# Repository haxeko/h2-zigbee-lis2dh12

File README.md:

# Activity Badge — ESP32-H2 + LIS2DH12 + Zigbee

Thẻ đeo (wearable badge) giám sát mức độ hoạt động của công nhân trên công trình.
LIS2DH12 lấy mẫu gia tốc liên tục ở 1 Hz, ESP32-H2 tính `activity_score` mỗi phút và gửi về
Zigbee2MQTT với vai trò Zigbee Sleepy End Device, chạy bằng pin LiPo.

```
        USB-C 5 V                       3V3
   ┌──────────────┐   VBAT   ┌─────────┐      ┌──────────────────────┐   802.15.4
   │ MCP73831     ├────┬─────┤ RT9080  ├──┬───┤ ESP32-H2-WROOM-02C   │ ))) Zigbee ──► router ──► Zigbee2MQTT ──► MQTT
   │ sạc LiPo     │    │     │ LDO 3V3 │  │   │  GPIO4/5   I2C       │
   └──────────────┘  LiPo    └─────────┘  │   │  GPIO10    INT1 (đánh thức)
                    500 mAh               │   │  GPIO1/0   đo pin    │
                                          │   └──────────┬───────────┘
                                          │              │ I2C + INT1
                                          │   ┌──────────┴───────────┐
                                          └───┤ LIS2DH12             │  1 Hz, low-power, FIFO 32 mẫu
                                              └──────────────────────┘
```

## Thuật toán

```
a_mag = sqrt(ax² + ay² + az²)
a_dyn = |a_mag − 1 g|
sum_dyn += a_dyn ; sample_count += 1        (60 mẫu, lưu trong RTC memory)
activity_score = sum_dyn / sample_count     → gửi Zigbee → reset
```

## Nội dung repo

| Thư mục | Nội dung | Tài liệu |
|---|---|---|
| [`hardware/`](hardware/) | Project KiCad: schematic + **PCB 20 × 36 mm, 4 lớp, đã đi dây**, Gerber, BOM, toạ độ linh kiện | [hardware/README.md](hardware/README.md) |
| [`firmware/`](firmware/) | Project ESP-IDF cho ESP32-H2 (esp-zigbee-sdk 2.x) | [firmware/README.md](firmware/README.md) |
| [`zigbee2mqtt/`](zigbee2mqtt/) | External converter cho Zigbee2MQTT + test | [docs/zigbee2mqtt.md](docs/zigbee2mqtt.md) |
| [`docs/`](docs/) | Ước tính dòng tiêu thụ/pin, hướng dẫn join và kiểm thử | [docs/power.md](docs/power.md) |

## Bắt đầu nhanh

1. **Phần cứng**: mở `hardware/kicad/activity-badge.kicad_pro` bằng KiCad 7 trở lên (schematic và
   PCB). File sản xuất nằm ở `hardware/out/fab/`; đọc mục 9 của `hardware/README.md` trước khi đặt hàng.
2. **Firmware** (ESP-IDF v5.5 trở lên):

   ```bash
   cd firmware && idf.py set-target esp32h2 && idf.py build
   ```
   Nạp: giữ BOOT, nhấn RESET, thả BOOT, rồi `idf.py -p /dev/ttyACM0 flash`.
3. **Zigbee2MQTT**: chép `zigbee2mqtt/activity_badge.mjs` vào `external_converters/`, bật
   `advanced.enable_external_js`, bật Permit join, cấp nguồn cho badge.
4. Dữ liệu xuất hiện mỗi phút trên `zigbee2mqtt/<tên badge>`:

   ```json
   {"activity_score": 0.127, "battery": 86, "voltage": 4000, "linkquality": 120}
   ```

## Các quyết định thiết kế chính

| Quyết định | Lý do |
|---|---|
| Cảm biến lấy mẫu vào FIFO, MCU chỉ dậy 2 lần/phút theo ngắt watermark INT1 | MCU không phải dậy 60 lần/phút; LIS2DH12 chỉ tốn ~2 µA |
| INT1 nối vào GPIO10 | Chỉ GPIO7–14 (LP GPIO) đánh thức được ESP32-H2 khỏi deep sleep |
| `activity_score` gửi qua Analog Input (0x000C) PresentValue, pin qua Power Configuration (0x0001) | Cluster chuẩn, converter Z2M chỉ vài dòng |
| Firmware tự gửi Report Attributes tới coordinator | Không phụ thuộc binding/configure reporting, vốn dễ lỡ với thiết bị ngủ |
| Hai chế độ ngủ chọn bằng Kconfig: deep sleep (mặc định, theo đề bài) và light sleep | Ước tính light sleep cho thời lượng pin dài hơn ~4–5 lần ở chu kỳ 1 phút; xem [docs/power.md](docs/power.md) |
| LDO Iq 2 µA, mạch đo pin có công tắc, không thạch anh 32 kHz | Giảm dòng nền và BOM |
| PCB 20 × 36 mm, linh kiện một mặt, pin hàn dây ở mặt dưới, anten nhô khỏi mép board | Gọn (nằm trong diện tích cell 500 mAh), lắp ráp rẻ, anten không bị đồng và FR-4 che |

## Trạng thái kiểm chứng

| Hạng mục | Trạng thái |
|---|---|
| Firmware build (ESP-IDF v5.5.4, esp-zigbee-lib 2.1.0), cả deep sleep, light sleep và bản release | Đã build, không warning trong mã project |
| Thuật toán activity | Unit test trên PC (so với công thức số thực trên 200 000 mẫu ngẫu nhiên) |
| Converter Zigbee2MQTT | Chạy thử với zigbee-herdsman-converters 26.129.0 bằng báo cáo giả lập |
| Schematic KiCad | Netlist xuất từ KiCad được so khớp tự động với netlist thiết kế; ERC chưa chạy |
| PCB KiCad | DRC của KiCad: 0 lỗi, 0 net chưa nối; net của 155 pad khớp với schematic. Chưa có người rà soát layout |
| **Chạy trên phần cứng thật** | **Chưa.** Board chưa được chế tạo; hành vi Zigbee trên sóng, dòng tiêu thụ và hiệu năng anten chưa được kiểm tra |

Danh sách việc cần xác minh: mục 9 của [hardware/README.md](hardware/README.md) trước khi đặt PCB, và
mục 6 của [firmware/README.md](firmware/README.md) khi có board.

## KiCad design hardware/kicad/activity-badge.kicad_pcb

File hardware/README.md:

# Phần cứng — Activity Badge (ESP32-H2-WROOM-02C + LIS2DH12)

Board 20 × 36 mm, 4 lớp, linh kiện một mặt, cổng USB-C để sạc và nạp firmware. Anten của module nhô
6 mm ra ngoài mép trên, nên tổng chiều dài là 42 mm.

> **Trạng thái.** Schematic và PCB được sinh bằng script, PCB đã qua DRC của KiCad (0 lỗi, 0 net
> chưa nối) và khớp netlist với schematic. Thiết kế **chưa được chế tạo và chưa có kỹ sư layout rà
> soát**; xem mục 9 trước khi đặt hàng.

## 1. File trong thư mục này

| File | Nội dung |
|---|---|
| `kicad/activity-badge.kicad_pro`, `.kicad_sch`, `.kicad_pcb` | Project KiCad (định dạng KiCad 7, mở được bằng KiCad 7/8/9) |
| `kicad/badge.kicad_sym` | Symbol ESP32-H2-WROOM-02C (thư viện chuẩn của KiCad và của Espressif chưa có module này) |
| `kicad/badge.pretty/` | Footprint module (theo "Recommended PCB Land Pattern" của datasheet v1.2, có vùng cấm đồng dưới anten) và footprint pad hàn dây pin |
| `out/activity-badge.pdf` | Sơ đồ nguyên lý |
| `out/pcb-front.pdf`, `out/pcb-back.pdf`, `out/*.png` | Bản vẽ PCB mặt trên / mặt dưới |
| `out/activity-badge.net`, `out/bom.csv` | Netlist KiCad, BOM |
| `out/drc-report.txt` | Báo cáo DRC của KiCad cho PCB |
| `out/fab/activity-badge-gerbers.zip` | Gerber X2 (4 lớp đồng, mask, paste, silkscreen, outline) + file khoan Excellon |
| `out/fab/activity-badge-pos.csv` | Toạ độ linh kiện cho máy gắp đặt |
| `gen/gen_kicad.py` | Sinh schematic, symbol, footprint, BOM, netlist từ một danh sách linh kiện + net duy nhất, rồi tự kiểm tra |
| `gen/gen_pcb.py`, `gen/router.py` | Dựng PCB bằng API `pcbnew`: đặt linh kiện, đi dây, đổ đồng, chạy DRC |
| `gen/fab_outputs.py` | Xuất Gerber, file khoan, toạ độ linh kiện, bản vẽ PDF |

Sinh lại toàn bộ (cần KiCad ≥ 7; `gen_pcb.py` phải chạy bằng Python có module `pcbnew` của KiCad):

```bash
python3 hardware/gen/gen_kicad.py
```

```bash
/usr/bin/python3 hardware/gen/gen_pcb.py
```

```bash
python3 hardware/gen/fab_outputs.py
```

## 2. Cây nguồn

```
USB-C VBUS 5 V ──► MCP73831 (sạc 213 mA) ──► VBAT (LiPo 1S 3,0–4,2 V) ──► RT9080-3.3 (Iq 2 µA) ──► +3V3
                                                │                                      ├─ ESP32-H2-WROOM-02C
                                                └─ Q1/Q2 + chia áp 1:2 ─► ADC (GPIO1)  └─ LIS2DH12 (luôn cấp điện)
```

- **LDO thay vì buck**: hiệu suất LDO từ 3,8 V xuống 3,3 V đã ~87 %, và ở tải µA dòng tĩnh của bộ
  nguồn mới là yếu tố quyết định. RT9080 có Iq 2 µA và chịu được 600 mA (datasheet module yêu cầu
  nguồn cấp ≥ 350 mA).
- Khi pin xuống dưới ~3,4 V LDO vào vùng sụt áp, +3V3 bám theo VBAT; module làm việc tới 3,0 V.
- LIS2DH12 không được cắt nguồn: nó phải lấy mẫu liên tục trong lúc MCU ngủ.
- Cell LiPo phải là loại **có mạch bảo vệ (PCM)**.
- **Nối pin khi dùng và khi nạp firmware qua USB.** Board không có đường nguồn riêng từ VBUS tới
  LDO: khi chỉ cắm USB, mọi dòng tải đều đi qua IC sạc. Hành vi của MCP73831 khi không có pin (ngắt
  sạc rồi sạc lại liên tục) chưa được kiểm chứng trên board này.

## 3. Sơ đồ chân ESP32-H2-WROOM-02C

| Chân module | Tên | GPIO | Net | Nối tới | Ghi chú |
|---|---|---|---|---|---|
| 1 | 3V3 | — | +3V3 | mặt phẳng +3V3 (lớp trong 2) | |
| 2 | EN | — | EN | SW2 (RESET), TP6 | module đã có sẵn RC 10 kΩ/1 µF |
| 3 | IO4 | GPIO4 | I2C_SDA | LIS2DH12 chân 4, R5 4,7 kΩ lên +3V3 | |
| 4 | IO5 | GPIO5 | I2C_SCL | LIS2DH12 chân 1, R6 4,7 kΩ lên +3V3 | |
| 5 | IO10 | GPIO10 | ACC_INT1 | LIS2DH12 chân 12 | **LP GPIO**: đánh thức từ deep sleep |
| 6 | IO11 | GPIO11 | ACC_INT2 | LIS2DH12 chân 11 | LP GPIO, dự phòng (firmware chưa dùng) |
| 7 | IO8 | GPIO8 | IO8_STRAP | R8 10 kΩ lên +3V3 | strapping: phải ở mức cao để vào download mode |
| 8 | IO9 | GPIO9 | BOOT | SW1, R7 10 kΩ lên +3V3, C11 100 nF, TP7 | strapping BOOT + nút người dùng, LP GPIO |
| 9, 13, 29 | GND | — | GND | mặt phẳng GND (lớp trong 1) | 29 = pad tản nhiệt dưới module |
| 10 | IO12 | GPIO12 | — | không nối | LP GPIO còn trống |
| 11, 12 | IO13, IO14 | GPIO13/14 | — | không nối | chân XTAL 32 kHz, không dùng |
| 14 | VBAT | — | +3V3 | C6 100 nF + C5 10 µF ngay dưới chân | mặc định nối 3V3 bên trong module |
| 15 | IO22 | GPIO22 | LED_STATUS | R9 2,2 kΩ → D1 → GND | tích cực mức cao |
| 16–19 | NC | — | — | không nối | |
| 20 | IO25 | GPIO25 | — | không nối | strapping nguồn JTAG, bị bỏ qua với eFuse mặc định |
| 21 | RXD0 | GPIO23 | UART_RX | TP5 | console/nạp qua UART |
| 22 | TXD0 | GPIO24 | UART_TX | TP4 | console (115200) |
| 23 | IO26 | GPIO26 | USB_DN | R15 0 Ω → U5 → USB-C D− | USB-Serial-JTAG |
| 24 | IO27 | GPIO27 | USB_DP | R14 0 Ω → U5 → USB-C D+ | USB-Serial-JTAG |
| 25, 26 | IO3, IO2 | GPIO3/2 | — | không nối | còn trống (ADC1_CH2/CH1) |
| 27 | IO1 | GPIO1 | VBAT_SENSE | điểm giữa R12/R13, C10 10 nF | ADC1_CH0 |
| 28 | IO0 | GPIO0 | VBAT_SENSE_EN | cực G của Q2, R11 1 MΩ xuống GND | mức cao = bật mạch chia áp |

Sơ đồ chân này trùng với `firmware/main/board.h`; việc thiết kế PCB không đổi chân nào.

### Kết nối ESP32-H2-WROOM-02C ↔ LIS2DH12 (LGA-12)

| LIS2DH12 | Tên | Nối tới | Ghi chú |
|---|---|---|---|
| 1 | SCL/SPC | GPIO5 (module chân 4) | I2C 400 kHz, kéo lên 4,7 kΩ |
| 2 | CS | +3V3 | mức cao = chế độ I2C |
| 3 | SDO/SA0 | +3V3 | địa chỉ I2C 0x19 (nối GND thì là 0x18) |
| 4 | SDA/SDI/SDO | GPIO4 (module chân 3) | kéo lên 4,7 kΩ |
| 5 | Res | GND | |
| 6, 7, 8 | GND | GND | |
| 9 | VDD | +3V3 | C7 100 nF + C8 10 µF sát chân |
| 10 | VDD_IO | +3V3 | C9 100 nF sát chân |
| 11 | INT2 | GPIO11 (module chân 6) | dự phòng: ngắt chuyển động/rơi tự do |
| 12 | INT1 | GPIO10 (module chân 5) | ngắt watermark FIFO, tích cực mức cao, push-pull |

Vì sao chọn các chân này:

- **INT1/INT2 phải vào LP GPIO (GPIO7–14)** vì chỉ các chân này dùng được làm nguồn đánh thức EXT1
  khi deep sleep. GPIO8/9 là strapping, GPIO13/14 là chân thạch anh 32 kHz, nên còn GPIO10/11/12.
- I2C trên GPIO4/5: không phải strapping, nằm cạnh GPIO10/11 trên cùng một cạnh module. (GPIO2–5
  là chân JTAG ngoài, nhưng mặc định ESP32-H2 dùng JTAG qua USB nên các chân này tự do.)
- GPIO26/27 dành cho USB, GPIO23/24 cho UART0, GPIO0/1 cho đo pin (GPIO1 có ADC).

## 4. Các khối mạch

**USB-C + ESD.** J1 (USB 2.0, 16 chân). CC1, CC2 mỗi chân một điện trở 5,1 kΩ xuống GND để nguồn
USB-C cấp 5 V. D+/D− qua U5 USBLC6-2SC6 rồi R14/R15 (0 Ω, chỗ để chỉnh tín hiệu) tới GPIO27/26.
Cổng này vừa sạc vừa nạp firmware/JTAG qua USB-Serial-JTAG của ESP32-H2, không cần chip USB-UART.

**Sạc LiPo.** U4 MCP73831T-2ACI/OT, 4,20 V. R3 = 4,7 kΩ → dòng sạc 1000 V / 4,7 kΩ ≈ 213 mA (hợp
với cell ≥ 400 mAh; đổi R3 nếu dùng cell khác: 10 kΩ → 100 mA, 2 kΩ → 500 mA). D2 sáng khi đang sạc
(VBUS → R4 → D2 → STAT), lấy điện từ VBUS nên không hao pin.

**Pin.** J2 là hai pad hàn dây 2 × 3 mm ở **mặt dưới**, ngay dưới cổng USB-C, có in "+" và "−".
Chọn pad hàn thay cho đầu nối để board gọn hơn (đầu nối JST-PH chiếm khoảng 8 × 8 mm mặt trên) và
chắc hơn khi thẻ bị rung lắc; đổi lại, thay pin phải dùng mỏ hàn.

**LDO 3,3 V.** U3 RT9080-33GJ5, EN nối VBAT (luôn bật). C3 1 µF ở ngõ vào, C4 22 µF ở ngõ ra để đỡ
bước tải từ µA lên hàng chục mA khi radio bật.

**MCU.** U1 ESP32-H2-WROOM-02C-H4S (4 MB flash, anten PCB). R8 kéo GPIO8 lên, R7 kéo GPIO9 lên.

**Gia tốc kế.** U2 LIS2DH12TR, I2C địa chỉ 0x19.

**Đo pin có công tắc.** Q1 (P-MOSFET AO3401A) nối VBAT vào mạch chia R12/R13 (100 kΩ/100 kΩ, 1 %)
chỉ khi GPIO0 ở mức cao (qua Q2 2N7002 kéo cực G của Q1 xuống). Khi tắt, dòng tiêu thụ chỉ còn dòng
rò của MOSFET và chân ADC ở 0 V (không bao giờ vượt quá 3,3 V). C10 10 nF giữ điện áp cho ADC lấy
mẫu; hằng số thời gian 0,5 ms nên firmware chờ 5 ms rồi đo.

**Nút và LED.** SW1 = BOOT/người dùng (GPIO9): nhấn ngắn để thức và ghép nối, giữ 5 s để factory
reset, giữ khi nhấn RESET để vào download mode. SW2 = RESET (EN). Hai nút loại 3 × 2,5 mm (Omron
B3U-1000P) nằm hai bên cổng USB-C. D1 = LED trạng thái.

**Test pad.** 7 pad tròn 1 mm ở mặt dưới, có in tên: EN, 3V3, GND, BOOT, RX, TX (một hàng phía
trên) và VBAT (góc dưới): đủ để nạp và kiểm tra bằng đồ gá pogo-pin.

## 5. BOM

Bản đầy đủ theo từng mã tham chiếu: [`out/bom.csv`](out/bom.csv). Mã linh kiện của điện trở, tụ,
LED và nút nhấn trong file đó chỉ là gợi ý ("or equivalent"), chưa đối chiếu với nhà phân phối.

| Ref | Giá trị / mã linh kiện | Footprint KiCad | Ghi chú |
|---|---|---|---|
| U1 | ESP32-H2-WROOM-02C-H4S | `badge:ESP32-H2-WROOM-02C` | 18 × 20 × 3,2 mm |
| U2 | LIS2DH12TR | `Package_LGA:LGA-12_2x2mm_P0.5mm` | |
| U3 | RT9080-33GJ5 | `Package_TO_SOT_SMD:TSOT-23-5` | thay thế cùng chân: XC6220B331MR-G (Iq ~8 µA), TPS7A0533PDBVR (Iq 1 µA, 200 mA) |
| U4 | MCP73831T-2ACI/OT | `Package_TO_SOT_SMD:SOT-23-5` | |
| U5 | USBLC6-2SC6 | `Package_TO_SOT_SMD:SOT-23-6` | |
| Q1 | AO3401A | `Package_TO_SOT_SMD:SOT-23` | P-MOSFET |
| Q2 | 2N7002 | `Package_TO_SOT_SMD:SOT-23` | N-MOSFET (hoặc BSS138) |
| J1 | USB-C 16P, HRO TYPE-C-31-M-12 | `Connector_USB:USB_C_Receptacle_HRO_TYPE-C-31-M-12` | |
| J2 | pad hàn dây pin | `badge:BatteryPads_1x02_P4.0mm` | không có linh kiện |
| SW1, SW2 | Omron B3U-1000P | `Button_Switch_SMD:SW_SPST_B3U-1000P` | 3 × 2,5 mm |
| D1 | LED xanh lá 0603 | `LED_SMD:LED_0603_1608Metric` | trạng thái |
| D2 | LED cam 0603 | `LED_SMD:LED_0603_1608Metric` | đang sạc |
| R1, R2 | 5,1 kΩ | `Resistor_SMD:R_0402_1005Metric` | CC1, CC2 |
| R3 | 4,7 kΩ 1 % | 0402 | PROG: dòng sạc 213 mA |
| R4 | 1 kΩ | 0402 | LED sạc |
| R5, R6 | 4,7 kΩ | 0402 | kéo lên I2C |
| R7, R8 | 10 kΩ | 0402 | kéo lên GPIO9, GPIO8 |
| R9 | 2,2 kΩ | 0402 | LED trạng thái |
| R10, R11 | 1 MΩ | 0402 | phân cực Q1, Q2 |
| R12, R13 | 100 kΩ 1 % | 0402 | chia áp pin |
| R14, R15 | 0 Ω | 0402 | nối tiếp USB D+/D− |
| C1 | 10 µF 16 V X5R | `Capacitor_SMD:C_0603_1608Metric` | VBUS |
| C2, C5, C8 | 10 µF | 0603 | VBAT, module 3V3, VDD cảm biến |
| C3 | 1 µF | 0402 | ngõ vào LDO |
| C4 | 22 µF | `Capacitor_SMD:C_0805_2012Metric` | ngõ ra LDO |
| C6, C7, C9, C11 | 100 nF | `Capacitor_SMD:C_0402_1005Metric` | lọc nguồn module, VDD, VDD_IO; chống rung nút |
| C10 | 10 nF | 0402 | lọc ADC |
| TP1–TP7 | pad thử 1 mm | `TestPoint:TestPoint_Pad_D1.0mm` | mặt dưới, không có linh kiện |
| — | Cell LiPo 1S 400–600 mAh có PCM, dây hàn | — | ví dụ cỡ 502535 (25 × 35 mm), đặt dưới board |

## 6. PCB

| Thông số | Giá trị |
|---|---|
| Kích thước | 20 × 36 mm, bo góc R 0,8 mm, dày 1,6 mm |
| Lớp | 4: F.Cu linh kiện + tín hiệu / In1.Cu GND liền / In2.Cu +3V3 / B.Cu tín hiệu |
| Lắp ráp | Toàn bộ 38 linh kiện ở mặt trên; mặt dưới chỉ có pad pin và test pad |
| Luật thiết kế | Track/khe hở 0,15/0,15 mm; đường nguồn 0,3 mm; **via 0,6 mm, lỗ 0,3 mm**; cách mép 0,3 mm |
| Đồng | 228 đoạn track, 70 via (tất cả lỗ 0,3 mm); GND đổ trên cả lớp trên và lớp dưới |
| DRC KiCad | 0 lỗi, 0 net chưa nối (`out/drc-report.txt`) |

Bố trí:

```
        ┌──────────────────┐  ← anten của module nhô 6 mm ra ngoài mép trên (không có FR-4/đồng bên dưới)
   y=0  ├──────────────────┤
        │       U1         │  ESP32-H2-WROOM-02C; mặt dưới: hàng test pad EN 3V3 GND BOOT RX TX
  14,5  ├──────────────────┤
        │ U2 cảm biến  C5/C6  D1 │  trái: LIS2DH12 + kéo lên I2C     phải: mạch đo pin Q1/Q2
        │ U4 sạc     R14/R15  U3 │  trái: MCP73831                  phải: LDO RT9080 + C4
        │           U5 ESD       │
  28    │ SW1 [  USB-C J1  ] SW2 │  mặt dưới: pad pin "+" "−" dưới cổng USB-C
   36   └──────────────────┘
```

Cách đi dây:

- **Tín hiệu của module đi lớp dưới.** Mỗi chân cạnh module có một đoạn ngắn và một via ngay sát
  ("hàng rào via"); phía dưới thân module ở lớp trên chỉ còn đồng GND.
- **Hai mặt phẳng trong không bị cắt.** Mọi tín hiệu nằm ở lớp trên và lớp dưới; In1 là GND liền,
  In2 là +3V3. Mỗi chân GND/+3V3 có via riêng xuống mặt phẳng.
- **Tụ lọc của module** (C6, C5) nằm ngay dưới chân 13 (GND) và 14 (3V3), nối bằng hai đường thẳng 0,3 mm.
- **USB-C**: bốn pad D+/D− bước 0,5 mm được nối chéo ngay phía trên đầu nối (một via 0,6 mm cho
  D+, đường D− bên cạnh né sớm sang trái để đủ khe hở), đi qua U5 rồi R14/R15 tới chân 23/24 của
  module; đoạn dưới thân module nằm ở lớp dưới.
- **LIS2DH12**: không có track hay via dưới thân linh kiện; I2C đi thẳng sang điện trở kéo, INT1/INT2
  đi lên phía module.
- Các chỗ khó (USB-C, LIS2DH12, tụ lọc, hàng rào via) được **vẽ tay bằng toạ độ** trong
  `pre_routes()` của `gen_pcb.py`; phần còn lại do bộ đi dây lưới 0,05 mm trong `router.py` tự tìm
  (KiCad không có autorouter). Vì các đoạn vẽ tay gắn với toạ độ, khi dời linh kiện trong bảng
  `PLACE` phải sửa cả `pre_routes()`. Via vẽ tay nào bộ đi dây không cần tới sẽ được gỡ ở bước dọn cuối.

Board còn có thể ngắn hơn khoảng 2 mm nếu xếp dày hơn bằng tay, hoặc ngắn hơn nhiều (~20 × 26 mm)
nếu chấp nhận lắp linh kiện hai mặt. Với cell 500 mAh cỡ 25 × 35 mm đặt dưới board thì 20 × 36 mm
đã nằm gọn trong diện tích của pin.

### Đặt sản xuất

- PCB 4 lớp, FR-4 1,6 mm (1,0 mm cũng được nếu cần nhẹ hơn), đồng 1 oz ngoài / 0,5 oz trong.
- Năng lực cần có: track/khe hở 0,15 mm; via đường kính 0,6 mm, lỗ 0,3 mm (vành khuyên 0,15 mm).
  Lỗ nhỏ nhất trên board là 0,3 mm; các lỗ còn lại là 0,6 mm (chân vỏ USB-C) và 0,65 mm (chốt định
  vị USB-C, không mạ). Đây là mức tiêu chuẩn, thường không bị tính phụ phí.
- Upload `out/fab/activity-badge-gerbers.zip`. File toạ độ linh kiện dùng tên cột của KiCad
  (gốc ở góc trên trái, Y âm); nhà lắp ráp có thể yêu cầu đổi tên cột và kiểm tra lại góc xoay.
- Module U1 nhô ra ngoài mép board 6 mm: báo cho nhà lắp ráp và chừa khoảng trống ở mép đó khi ghép panel.

## 7. Nguyên tắc layout đã áp dụng

**Anten.** Phần anten của module nằm ngoài board nên không có FR-4 hay đồng bên dưới. Pin LiPo (vỏ
nhôm), vít và kẹp kim loại của thẻ không được nằm chồng lên vùng này: đặt pin lùi về phía cổng USB.
Thẻ đeo trên người bị cơ thể hấp thụ sóng 2,4 GHz, nên hướng mặt anten ra ngoài và đo vùng phủ khi
đang đeo thật. Vỏ hộp bằng nhựa, không sơn dẫn điện, không tem kim loại ở vùng anten.

**Nguồn và tụ lọc.** C6/C5 sát chân 13/14 của module; C4 sát ngõ ra LDO, C3 sát ngõ vào; C1, C2
sát chân VDD và VBAT của MCP73831; C7/C8 và C9 sát chân 9 và 10 của LIS2DH12.

**Mặt phẳng GND.** Lớp trong 1 là GND liền dưới toàn bộ mạch. Pad tản nhiệt của module có 2 via
GND; có thể thêm via khâu GND ở các khoảng trống nếu muốn.

**LIS2DH12.** Đặt cách mép board gần 3 mm, xa nút nhấn và đầu nối USB (ứng suất cơ học làm lệch
offset), xa IC sạc và LDO (nhiệt làm trôi offset). Hàn bằng reflow, không hàn tay bằng mỏ hàn.

**Cơ khí và môi trường công trường.** Cố định pin bằng băng keo xốp và giữ dây pin để mối hàn không
chịu lực. Bụi, mồ hôi, mưa: phủ conformal coating (che cổng USB-C, nút, test pad) hoặc dùng vỏ có
gioăng. Nút nhấn hở là đường vào của tĩnh điện từ tay người; nếu vỏ có khe gần nút nên thêm TVS.

## 8. Kiểm tra khi lắp board đầu tiên

1. Chưa hàn module: cấp VBAT 3,8 V vào pad pin, đo +3V3 = 3,30 V tại TP 3V3, dòng không tải cỡ vài µA.
2. Cắm USB với nguồn giả lập pin: D2 sáng, dòng sạc ≈ 213 mA.
3. Hàn module, nạp firmware, xem log trên pad TX: thấy `LIS2DH12 running`.
4. Đo INT1 bằng oscilloscope: lên mức cao mỗi ~30 s, xuống ngay khi MCU đọc FIFO.
5. Đo dòng ngủ tại VBAT (xem [docs/power.md](../docs/power.md)): kỳ vọng ~12 µA ở deep sleep.
6. Ghép nối với Zigbee2MQTT (xem [docs/zigbee2mqtt.md](../docs/zigbee2mqtt.md)).

## 9. Cần xác minh trước khi đặt hàng

1. **Mở project trong KiCad và tự rà soát PCB**: chạy lại DRC, chạy ERC cho schematic (KiCad 7
   không có ERC dòng lệnh nên chưa chạy), xem 3D. Bố trí và đi dây do script sinh ra; DRC chỉ bảo
   đảm khoảng cách và kết nối, không thay được con mắt của người làm layout.
2. **Thứ tự chân RT9080-33GJ5** (1 VIN, 2 GND, 3 EN, 4 NC, 5 VOUT) với datasheet Richtek. Đây là
   thứ tự chân SOT-23-5 phổ biến của LDO và trùng với các linh kiện thay thế nêu trong BOM, nhưng
   tôi không truy cập được datasheet Richtek để kiểm tra trực tiếp.
3. **Thứ tự chân LIS2DH12** với datasheet ST. Bảng ở mục 3 khớp với symbol LIS2DE12 (cùng họ, cùng
   vỏ LGA-12) trong thư viện KiCad, nhưng tôi không tải được datasheet từ st.com.
4. **Footprint ESP32-H2-WROOM-02C**: in tỉ lệ 1:1 và ướm với module thật. Kích thước lấy từ hình
   "Recommended PCB Land Pattern" của datasheet v1.2 (pad 0,9 × 1,5 mm, bước 1,5 mm, 9 + 10 + 9 pad,
   pad GND gồm hai mảng 2,8 × 0,55 mm và 2,8 × 1,6 mm).
5. **Cổng USB-C**: footprint là của HRO TYPE-C-31-M-12, mặt trước đầu nối nhô 0,65 mm khỏi mép
   board. Kiểm tra theo đúng mã linh kiện mua được và theo vỏ hộp.
6. **Cực tính pin**: pad "+" là pad gần nút BOOT (SW1) khi nhìn từ mặt trên, tức nằm bên phải khi
   lật board nhìn từ mặt dưới với cổng USB quay xuống. Mạch không có bảo vệ ngược cực.
7. Nên bổ sung trong firmware ngưỡng **khoá khi pin yếu** (ví dụ dưới 3,3 V thì ngừng phát sóng) trước
   khi sản xuất, để tránh vòng lặp reset khi pin cạn; hiện phần này dựa vào mạch bảo vệ của cell.

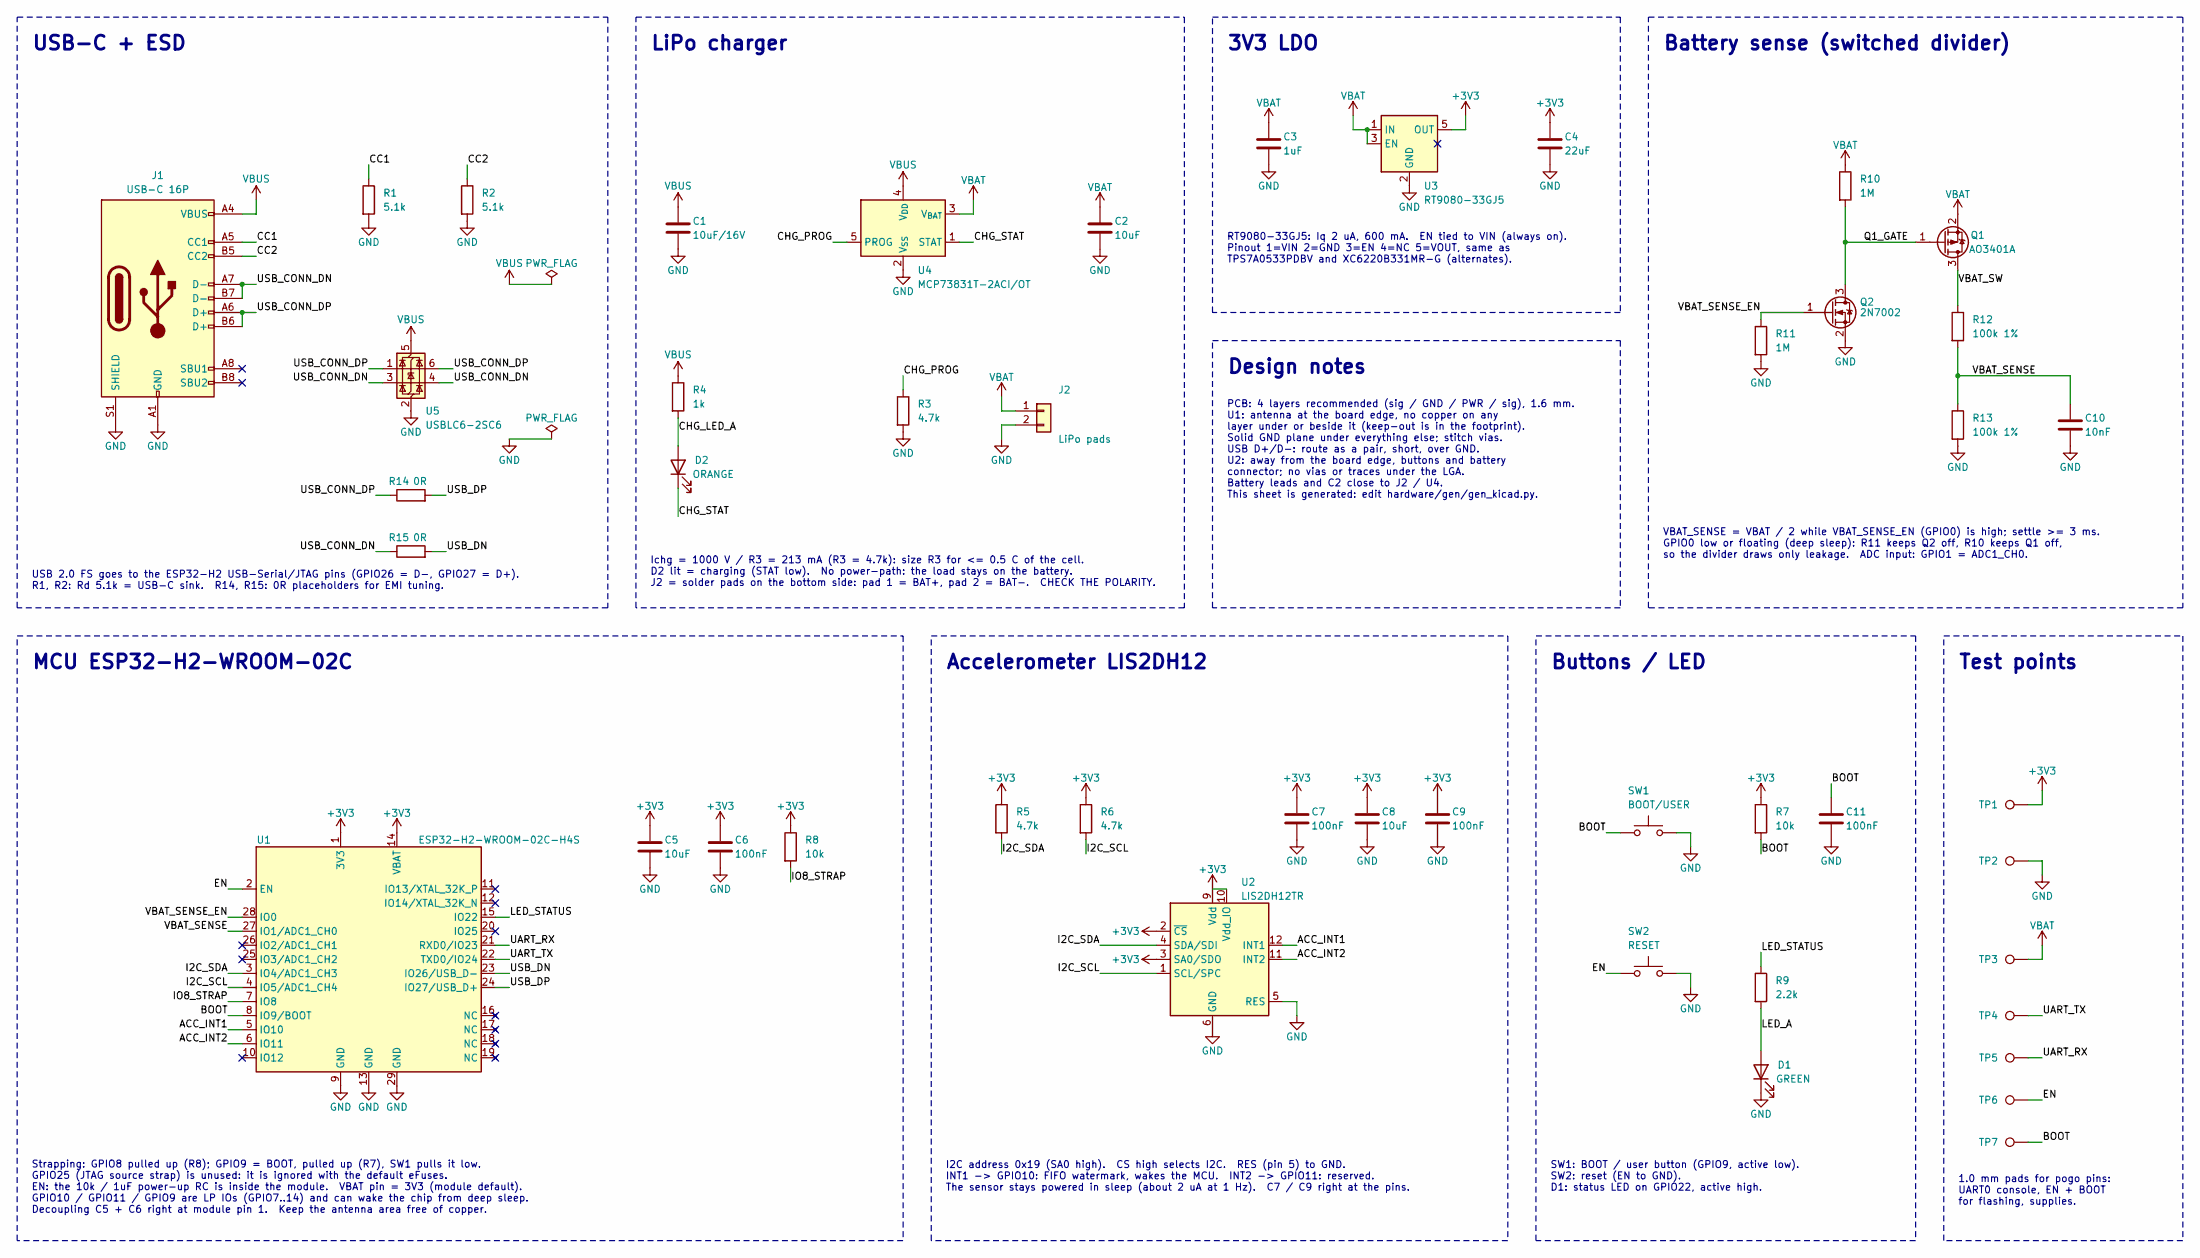
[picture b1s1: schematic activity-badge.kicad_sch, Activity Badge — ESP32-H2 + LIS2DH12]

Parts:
C1: 10uF/16V; C_0603_1608Metric; MPN CL10A106KO8NNNC
C2, C5, C8: 10uF; C_0603_1608Metric; MPN CL10A106KP8NNNC
C3: 1uF; C_0402_1005Metric; MPN CL05A105KO5NNNC
C4: 22uF; C_0805_2012Metric; MPN CL21A226MQQNNNE
C6, C7, C9, C11: 100nF; C_0402_1005Metric; MPN CL05B104KO5NNNC
C10: 10nF; C_0402_1005Metric; MPN CL05B103KB5NNNC
D1: GREEN; LED_0603_1608Metric; MPN LTST-C191KGKT
D2: ORANGE; LED_0603_1608Metric; MPN LTST-C191KFKT
J1: USB-C 16P; USB_C_Receptacle_HRO_TYPE-C-31-M-12; MPN TYPE-C-31-M-12
J2: LiPo pads; BatteryPads_1x02_P4.0mm
Q1: AO3401A; SOT-23; MPN AO3401A
Q2: 2N7002; SOT-23; MPN 2N7002
R1, R2: 5.1k; R_0402_1005Metric; MPN RC0402FR-075K1L
R3, R5, R6: 4.7k; R_0402_1005Metric; MPN RC0402FR-074K7L
R4: 1k; R_0402_1005Metric; MPN RC0402FR-071KL
R7, R8: 10k; R_0402_1005Metric; MPN RC0402FR-0710KL
R9: 2.2k; R_0402_1005Metric; MPN RC0402FR-072K2L
R10, R11: 1M; R_0402_1005Metric; MPN RC0402FR-071ML
R12, R13: 100k 1%; R_0402_1005Metric; MPN RC0402FR-07100KL
R14, R15: 0R; R_0402_1005Metric; MPN RC0402JR-070RL
SW1: BOOT/USER; SW_SPST_B3U-1000P; MPN B3U-1000P
SW2: RESET; SW_SPST_B3U-1000P; MPN B3U-1000P
TP1: +3V3; TestPoint_Pad_D1.0mm
TP2: GND; TestPoint_Pad_D1.0mm
TP3: VBAT; TestPoint_Pad_D1.0mm
TP4: UART_TX; TestPoint_Pad_D1.0mm
TP5: UART_RX; TestPoint_Pad_D1.0mm
TP6: EN; TestPoint_Pad_D1.0mm
TP7: BOOT; TestPoint_Pad_D1.0mm
U1: ESP32-H2-WROOM-02C-H4S; ESP32-H2-WROOM-02C; MPN ESP32-H2-WROOM-02C-H4S
U2: LIS2DH12TR; LGA-12_2x2mm_P0.5mm; MPN LIS2DH12TR
U3: RT9080-33GJ5; TSOT-23-5; MPN RT9080-33GJ5
U4: MCP73831T-2ACI/OT; SOT-23-5; MPN MCP73831T-2ACI/OT
U5: USBLC6-2SC6; SOT-23-6; MPN USBLC6-2SC6

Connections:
+3V3: C4.1, C5.1, C6.1, C7.1, C8.1, C9.1, R5.1, R6.1, R7.1, R8.1, TP1.1, U1.1 (3V3), U1.14 (VBAT), U2.2 (~CS), U2.3 (SA0/SDO), U2.9 (Vdd), U2.10 (Vdd_IO), U3.5 (OUT)
/ACC_INT1: U1.5 (IO10), U2.12 (INT1)
/ACC_INT2: U1.6 (IO11), U2.11 (INT2)
/BOOT: C11.1, R7.2, SW1.1, TP7.1, U1.8 (IO9/BOOT)
/CC1: J1.A5 (CC1), R1.1
/CC2: J1.B5 (CC2), R2.1
/CHG_LED_A: D2.2 (A), R4.2
/CHG_PROG: R3.1, U4.5 (PROG)
/CHG_STAT: D2.1 (K), U4.1 (STAT)
/EN: SW2.1, TP6.1, U1.2 (EN)
/I2C_SCL: R6.2, U1.4 (IO5/ADC1_CH4), U2.1 (SCL/SPC)
/I2C_SDA: R5.2, U1.3 (IO4/ADC1_CH3), U2.4 (SDA/SDI)
/IO8_STRAP: R8.2, U1.7 (IO8)
/LED_A: D1.2 (A), R9.2
/LED_STATUS: R9.1, U1.15 (IO22)
/Q1_GATE: Q1.1 (G), Q2.3 (D), R10.2
/UART_RX: TP5.1, U1.21 (RXD0/IO23)
/UART_TX: TP4.1, U1.22 (TXD0/IO24)
/USB_CONN_DN: J1.A7 (D-), J1.B7 (D-), R15.1, U5.3 (I/O2), U5.4 (I/O2)
/USB_CONN_DP: J1.A6 (D+), J1.B6 (D+), R14.1, U5.1 (I/O1), U5.6 (I/O1)
/USB_DN: R15.2, U1.23 (IO26/USB_D-)
/USB_DP: R14.2, U1.24 (IO27/USB_D+)
/VBAT_SENSE: C10.1, R12.2, R13.1, U1.27 (IO1/ADC1_CH0)
/VBAT_SENSE_EN: Q2.1 (G), R11.1, U1.28 (IO0)
/VBAT_SW: Q1.3 (D), R12.1
GND: C1.2, C2.2, C3.2, C4.2, C5.2, C6.2, C7.2, C8.2, C9.2, C10.2, C11.2, D1.1 (K), J1.A1 (GND), J1.A12 (GND), J1.B1 (GND), J1.B12 (GND), J1.S1 (SHIELD), J2.2, Q2.2 (S), R1.2, R2.2, R3.2, R11.2, R13.2, SW1.2, SW2.2, TP2.1, U1.9 (GND), U1.13 (GND), U1.29 (GND), U2.5 (RES), U2.6 (GND), U2.7 (GND), U2.8 (GND), U3.2 (GND), U4.2 (V_{SS}), U5.2 (GND)
VBAT: C2.1, C3.1, J2.1, Q1.2 (S), R10.1, TP3.1, U3.1 (IN), U3.3 (EN), U4.3 (V_{BAT})
VBUS: C1.1, J1.A4 (VBUS), J1.A9 (VBUS), J1.B4 (VBUS), J1.B9 (VBUS), R4.1, U4.4 (V_{DD}), U5.5 (VBUS)

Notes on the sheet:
USB-C + ESD
USB 2.0 FS goes to the ESP32-H2 USB-Serial/JTAG pins (GPIO26 = D-, GPIO27 = D+). R1, R2: Rd 5.1k = USB-C sink. R14, R15: 0R placeholders for EMI tuning.
LiPo charger
Ichg = 1000 V / R3 = 213 mA (R3 = 4.7k): size R3 for <= 0.5 C of the cell. D2 lit = charging (STAT low). No power-path: the load stays on the battery. J2 = solder pads on the bottom side: pad 1 = BAT+, pad 2 = BAT-. CHECK THE POLARITY.
3V3 LDO
RT9080-33GJ5: Iq 2 uA, 600 mA. EN tied to VIN (always on). Pinout 1=VIN 2=GND 3=EN 4=NC 5=VOUT, same as TPS7A0533PDBV and XC6220B331MR-G (alternates).
Design notes
PCB: 4 layers recommended (sig / GND / PWR / sig), 1.6 mm. U1: antenna at the board edge, no copper on any layer under or beside it (keep-out is in the footprint). Solid GND plane under everything else; stitch vias. USB D+/D-: route as a pair, short, over GND. U2: away from the board edge, buttons 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
Battery sense (switched divider)
VBAT_SENSE = VBAT / 2 while VBAT_SENSE_EN (GPIO0) is high; settle >= 3 ms. GPIO0 low or floating (deep sleep): R11 keeps Q2 off, R10 keeps Q1 off, so the divider draws only leakage. ADC input: GPIO1 = ADC1_CH0.
MCU ESP32-H2-WROOM-02C
Strapping: GPIO8 pulled up (R8); GPIO9 = BOOT, pulled up (R7), SW1 pulls it low. GPIO25 (JTAG source strap) is unused: it is ignored with the default eFuses. EN: the 10k / 1uF power-up RC is inside the module. VBAT pin = 3V3 (module default). GPIO10 / GPIO11 / GPIO9 are LP IOs (GPIO7..14) and can w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
Accelerometer LIS2DH12
I2C address 0x19 (SA0 high). CS high selects I2C. RES (pin 5) to GND. INT1 -> GPIO10: FIFO watermark, wakes the MCU. INT2 -> GPIO11: reserved. The sensor stays powered in sleep (about 2 uA at 1 Hz). C7 / C9 right at the pins.
Buttons / LED
SW1: BOOT / user button (GPIO9, active low). SW2: reset (EN to GND). D1: status LED on GPIO22, active high.
Test points
1.0 mm pads for pogo pins: UART0 console, EN + BOOT for flashing, supplies.

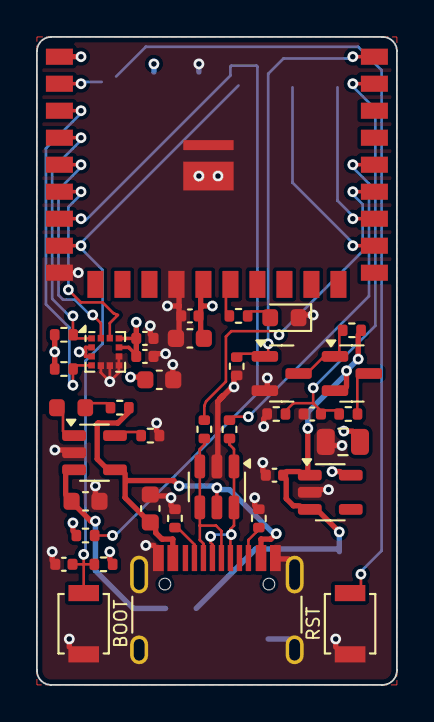
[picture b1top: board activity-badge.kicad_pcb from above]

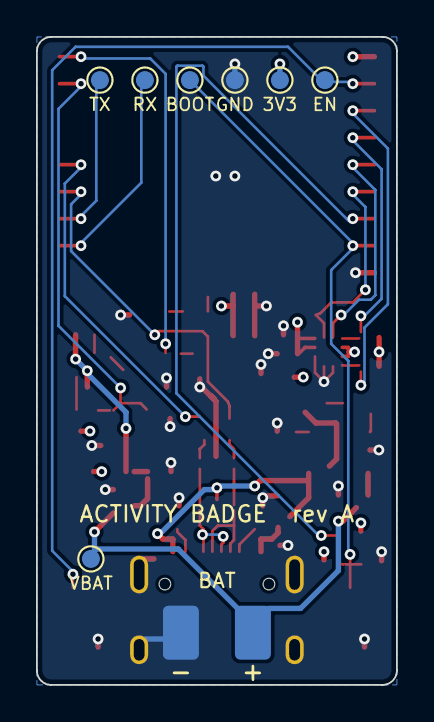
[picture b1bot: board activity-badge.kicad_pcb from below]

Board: 4 copper layers, 20.0 x 36.0 mm, 46 parts (8 on the bottom side), 28 nets.

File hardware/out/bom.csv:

Ref,Qty,Value,Description,Footprint,MPN,Notes
U1,1,ESP32-H2-WROOM-02C-H4S,"Espressif 802.15.4 / BLE module, ESP32-H2, 4 MB flash, PCB antenna",badge:ESP32-H2-WROOM-02C,ESP32-H2-WROOM-02C-H4S,Project-local symbol + footprint (datasheet v1.2 land pattern)
U2,1,LIS2DH12TR,"ST 3-axis accelerometer, I2C, LGA-12 2x2 mm",Package_LGA:LGA-12_2x2mm_P0.5mm,LIS2DH12TR,Drawn with the pin-compatible LIS2DE12 library symbol; I2C address 0x19 (SA0 = 1)
U3,1,RT9080-33GJ5,"Richtek 3.3 V LDO, 600 mA, Iq 2 uA, TSOT-23-5",Package_TO_SOT_SMD:TSOT-23-5,RT9080-33GJ5,"Pinout 1=VIN 2=GND 3=EN 4=NC 5=VOUT - verify against the datasheet; same-pinout alternates: TPS7A0533PDBV (200 mA), XC6220B331MR-G"
U4,1,MCP73831T-2ACI/OT,"Microchip single-cell Li-Po charger, 4.20 V, SOT-23-5",Package_TO_SOT_SMD:SOT-23-5,MCP73831T-2ACI/OT,
U5,1,USBLC6-2SC6,"ST USB ESD protection, SOT-23-6",Package_TO_SOT_SMD:SOT-23-6,USBLC6-2SC6,
Q1,1,AO3401A,"P-channel MOSFET -30 V, SOT-23 (battery-sense high-side switch)",Package_TO_SOT_SMD:SOT-23,AO3401A,or equivalent
Q2,1,2N7002,"N-channel MOSFET 60 V, SOT-23 (level shifter for Q1 gate)",Package_TO_SOT_SMD:SOT-23,2N7002,or equivalent
D1,1,GREEN,LED green 0603 (status),LED_SMD:LED_0603_1608Metric,LTST-C191KGKT,or equivalent
D2,1,ORANGE,LED orange 0603 (charging),LED_SMD:LED_0603_1608Metric,LTST-C191KFKT,or equivalent
J1,1,USB-C 16P,"USB Type-C receptacle, USB 2.0, 16 pin, SMD (HRO)",Connector_USB:USB_C_Receptacle_HRO_TYPE-C-31-M-12,TYPE-C-31-M-12,
J2,1,LiPo pads,"Solder pads for the LiPo leads (bottom side, 2.0 x 3.0 mm, 4 mm pitch)",badge:BatteryPads_1x02_P4.0mm,,"Pad 1 = BAT+, pad 2 = BAT-. No part to fit: solder the cell leads and secure them"
SW1,1,BOOT/USER,"Tactile switch SPST 3 x 2.5 mm, top actuated (Omron B3U)",Button_Switch_SMD:SW_SPST_B3U-1000P,B3U-1000P,GPIO9: boot strap + user button; or equivalent
SW2,1,RESET,"Tactile switch SPST 3 x 2.5 mm, top actuated (Omron B3U)",Button_Switch_SMD:SW_SPST_B3U-1000P,B3U-1000P,EN to GND; or equivalent
"R1, R2",2,5.1k,Resistor 5.1 k 1% 0402,Resistor_SMD:R_0402_1005Metric,RC0402FR-075K1L,or equivalent
R3,1,4.7k,Resistor 4.7 k 1% 0402,Resistor_SMD:R_0402_1005Metric,RC0402FR-074K7L,Ichg = 1000 V / R3; or equivalent
R4,1,1k,Resistor 1 k 1% 0402,Resistor_SMD:R_0402_1005Metric,RC0402FR-071KL,or equivalent
"R5, R6",2,4.7k,Resistor 4.7 k 1% 0402,Resistor_SMD:R_0402_1005Metric,RC0402FR-074K7L,or equivalent
"R7, R8",2,10k,Resistor 10 k 1% 0402,Resistor_SMD:R_0402_1005Metric,RC0402FR-0710KL,or equivalent
R9,1,2.2k,Resistor 2.2 k 1% 0402,Resistor_SMD:R_0402_1005Metric,RC0402FR-072K2L,or equivalent
"R10, R11",2,1M,Resistor 1 M 1% 0402,Resistor_SMD:R_0402_1005Metric,RC0402FR-071ML,or equivalent
"R12, R13",2,100k 1%,Resistor 100 k 1% 0402,Resistor_SMD:R_0402_1005Metric,RC0402FR-07100KL,or equivalent
"R14, R15",2,0R,Resistor 0 R 0402,Resistor_SMD:R_0402_1005Metric,RC0402JR-070RL,or equivalent
C1,1,10uF/16V,Capacitor 10 uF 16 V X5R 0603,Capacitor_SMD:C_0603_1608Metric,CL10A106KO8NNNC,or equivalent
"C2, C5, C8",3,10uF,Capacitor 10 uF 10 V X5R 0603,Capacitor_SMD:C_0603_1608Metric,CL10A106KP8NNNC,or equivalent
C3,1,1uF,Capacitor 1 uF 16 V X5R 0402,Capacitor_SMD:C_0402_1005Metric,CL05A105KO5NNNC,or equivalent
C4,1,22uF,Capacitor 22 uF 6.3 V X5R 0805,Capacitor_SMD:C_0805_2012Metric,CL21A226MQQNNNE,or equivalent
"C6, C7, C9, C11",4,100nF,Capacitor 100 nF 16 V X7R 0402,Capacitor_SMD:C_0402_1005Metric,CL05B104KO5NNNC,or equivalent
C10,1,10nF,Capacitor 10 nF 50 V X7R 0402,Capacitor_SMD:C_0402_1005Metric,CL05B103KB5NNNC,or equivalent
TP1,1,+3V3,Test pad 1.0 mm,TestPoint:TestPoint_Pad_D1.0mm,,No part to fit
TP2,1,GND,Test pad 1.0 mm,TestPoint:TestPoint_Pad_D1.0mm,,No part to fit
TP3,1,VBAT,Test pad 1.0 mm,TestPoint:TestPoint_Pad_D1.0mm,,No part to fit
TP4,1,UART_TX,Test pad 1.0 mm,TestPoint:TestPoint_Pad_D1.0mm,,No part to fit
TP5,1,UART_RX,Test pad 1.0 mm,TestPoint:TestPoint_Pad_D1.0mm,,No part to fit
TP6,1,EN,Test pad 1.0 mm,TestPoint:TestPoint_Pad_D1.0mm,,No part to fit
TP7,1,BOOT,Test pad 1.0 mm,TestPoint:TestPoint_Pad_D1.0mm,,No part to fit

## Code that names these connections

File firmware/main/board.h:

/*
 * Board pin map — activity badge, ESP32-H2-WROOM-02C.
 * Keep in sync with hardware/README.md (schematic net names in comments).
 */
#pragma once

#include "driver/gpio.h"
#include "hal/adc_types.h"

/* I2C bus to the LIS2DH12 (external 4.7 kΩ pull-ups to 3V3) */
#define BOARD_I2C_SDA_GPIO      GPIO_NUM_4   /* module pin 3,  net I2C_SDA */
#define BOARD_I2C_SCL_GPIO      GPIO_NUM_5   /* module pin 4,  net I2C_SCL */
#define BOARD_I2C_FREQ_HZ       400000
#define BOARD_LIS2DH12_ADDR     0x19         /* SA0 tied to VDD_IO */

/*
 * LIS2DH12 interrupt lines. Both are on LP GPIOs (GPIO7..14 on ESP32-H2), the
 * only pins that can wake the chip from deep sleep (EXT1).
 */
#define BOARD_ACC_INT1_GPIO     GPIO_NUM_10  /* module pin 5,  net ACC_INT1: FIFO watermark, active high */
#define BOARD_ACC_INT2_GPIO     GPIO_NUM_11  /* module pin 6,  net ACC_INT2: reserved, unused by firmware */

/* User/BOOT button: strapping pin GPIO9, LP GPIO, active low, 10 kΩ pull-up */
#define BOARD_BUTTON_GPIO       GPIO_NUM_9   /* module pin 8,  net BOOT */

/* Status LED, active high through 2.2 kΩ */
#define BOARD_LED_GPIO          GPIO_NUM_22  /* module pin 15, net LED_STATUS */

/*
 * Battery sense: VBAT -> P-FET switch -> 100k/100k divider -> ADC.
 * The divider only draws current while BOARD_VBAT_EN_GPIO is high.
 */
#define BOARD_VBAT_EN_GPIO      GPIO_NUM_0    /* module pin 28, net VBAT_SENSE_EN */
#define BOARD_VBAT_ADC_CHANNEL  ADC_CHANNEL_0 /* GPIO1, module pin 27, net VBAT_SENSE */
#define BOARD_VBAT_DIVIDER      2             /* V(bat) = V(adc) * 2 */
#define BOARD_VBAT_SETTLE_MS    5             /* RC of the divider node: 50 kΩ * 10 nF = 0.5 ms */

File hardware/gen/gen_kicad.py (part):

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            "Pinout 1=VIN 2=GND 3=EN 4=NC 5=VOUT, same as\n"
            "TPS7A0533PDBV and XC6220B331MR-G (alternates)."),
    "vsense": (2.54, 93.98,
               "VBAT_SENSE = VBAT / 2 while VBAT_SENSE_EN (GPIO0) is high; settle >= 3 ms.\n"
               "GPIO0 low or floating (deep sleep): R11 keeps Q2 off, R10 keeps Q1 off,\n"
               "so the divider draws only leakage.  ADC input: GPIO1 = ADC1_CH0."),
    "mcu": (2.54, 96.52,
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        # charge LED: VBUS - R4 - D2 - STAT
        a, b = ep("R4.2"), ep("D2.2")
        self.wire(a, b)
        self.label("CHG_LED_A", (a[0], (a[1] + b[1]) / 2), 0)
        done.update(("R4.2", "D2.2"))

        # status LED: GPIO22 - R9 - D1 - GND
        a, b = ep("R9.2"), ep("D1.2")
        self.wire(a, b)
        self.label("LED_A", (a[0], (a[1] + b[1]) / 2), 0)
        done.update(("R9.2", "D1.2"))

        # battery sense: Q1 gate node (R10 pull-up, Q2 drain)
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        node = (r10[0], g[1])
        self.path(r10, node, g)
        self.wire(q2d, node)
        self.label("Q1_GATE", (g[0] - 1.27, g[1]), 180)
        done.update(("Q1.1", "R10.2", "Q2.3"))

        # Q2 gate: GPIO0 with R11 pull-down
        g2, r11 = ep("Q2.1"), ep("R11.1")
        corner = (r11[0], g2[1])
        self.path(r11, corner, g2)
        self.label("VBAT_SENSE_EN", corner, 180)
        done.update(("Q2.1", "R11.1"))

        # switched divider: Q1 drain - R12 - (VBAT_SENSE) - R13 - GND, C10 across R13
        d1, r12a, r12b, r13a, c10 = ep("Q1.3"), ep("R12.1"), ep("R12.2"), ep("R13.1"), ep("C10.1")
        assert d1[0] == r12a[0] == r13a[0]
        self.wire(d1, r12a)
        self.label("VBAT_SW", (d1[0], round((d1[1] + r12a[1]) / 2 / 1.27) * 1.27), 0)
        self.wire(r12b, r13a)
        tap = (r12b[0], round((r12b[1] + r13a[1]) / 2 / 1.27) * 1.27)
        self.path(c10, (c10[0], tap[1]), tap)
        self.label("VBAT_SENSE", (tap[0] + 2.54, tap[1]), 0)
        done.update(("Q1.3", "R12.1", "R12.2", "R13.1", "C10.1"))

    # ---- finishing --------------------------------------------------------
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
